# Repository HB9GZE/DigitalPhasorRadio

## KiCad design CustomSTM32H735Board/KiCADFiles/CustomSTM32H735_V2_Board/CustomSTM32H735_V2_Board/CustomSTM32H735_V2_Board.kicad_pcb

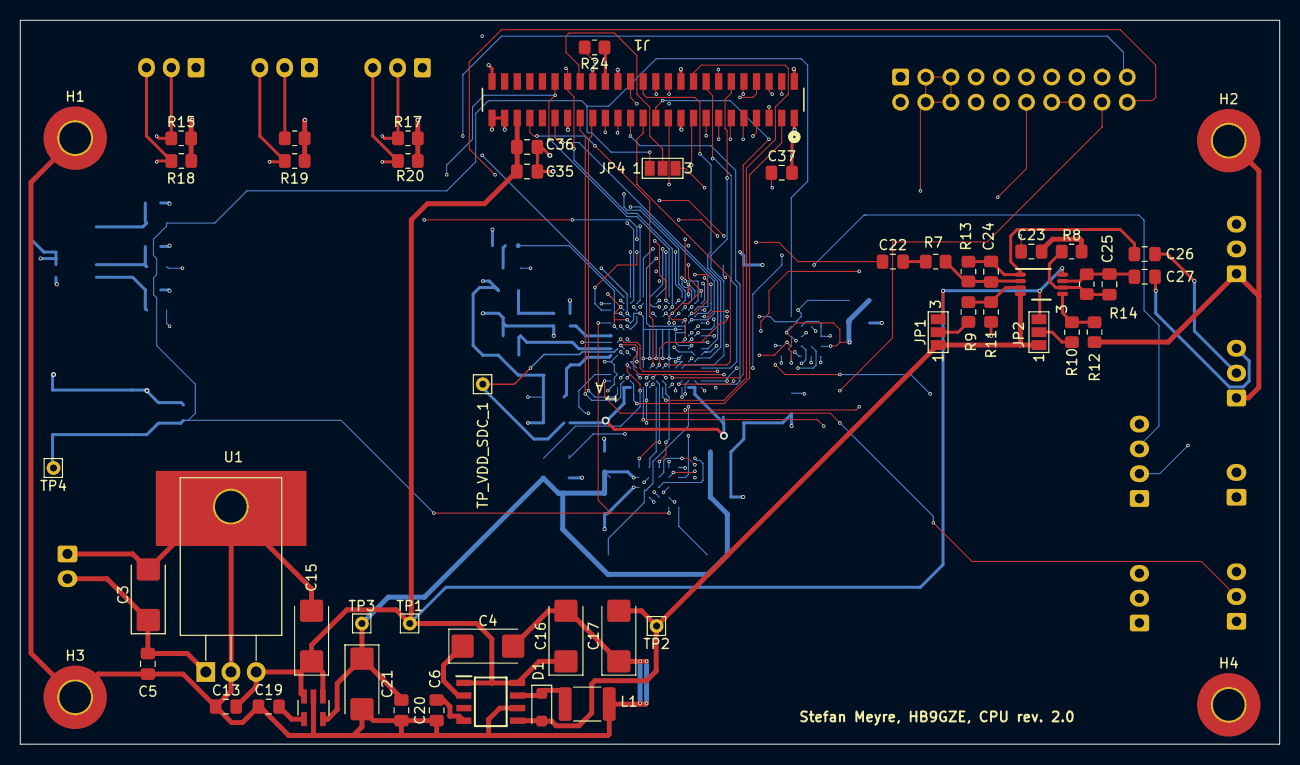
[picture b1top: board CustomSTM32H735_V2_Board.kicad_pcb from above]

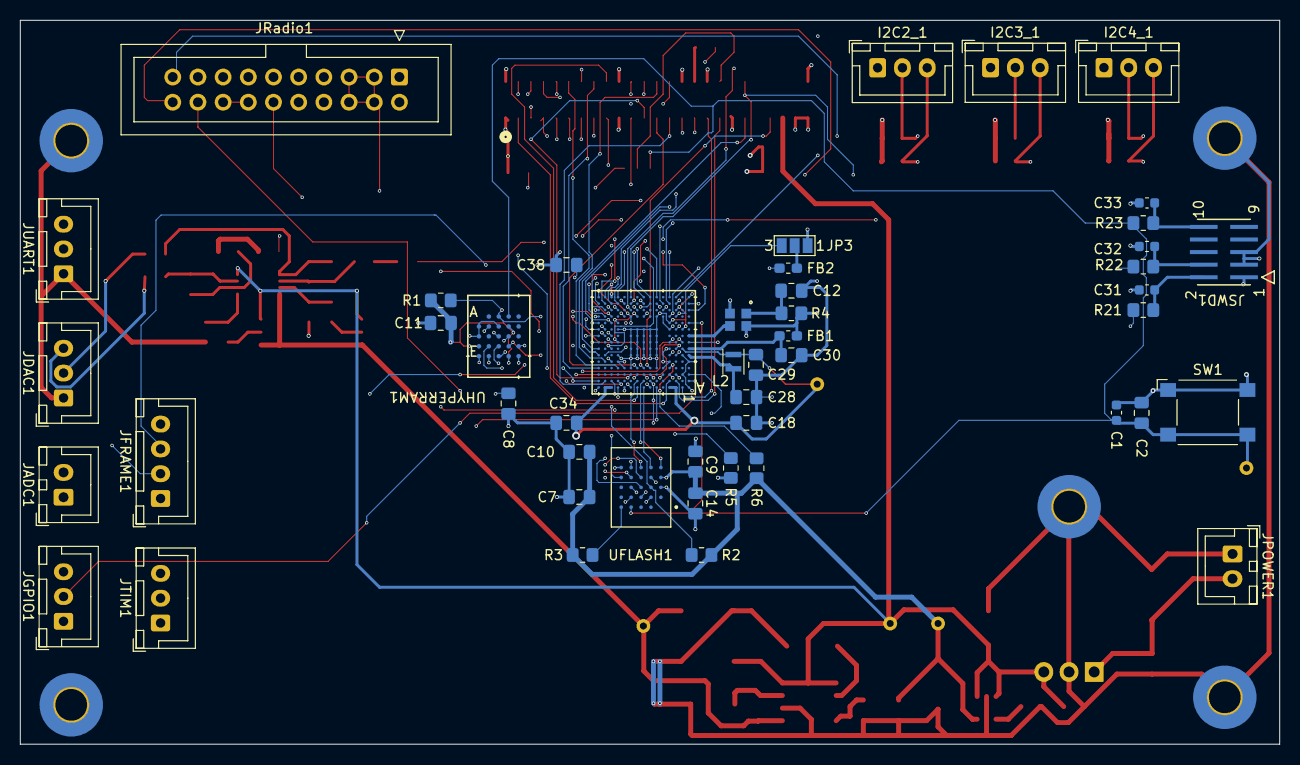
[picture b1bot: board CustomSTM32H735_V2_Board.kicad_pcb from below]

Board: 4 copper layers, 127.0 x 73.0 mm, 103 parts (48 on the bottom side), 122 nets.

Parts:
C1, C31, C32, C33: PGB1010603; C_0603_1608Metric
C2, C5, C7, C8, C9, C10, C11, C12, C13, C14, C20, C36, C37: 100nF; C_0805_2012Metric_Pad1.18x1.45mm_HandSolder
C3, C15: 47uF Tant. 25V; CP_EIA-6032-20_AVX-F_Pad2.25x2.35mm_HandSolder
C4, C21: 10uF Tant. 25V; CP_EIA-6032-20_AVX-F_Pad2.25x2.35mm_HandSolder
C6: optional: 82pF; C_0805_2012Metric_Pad1.18x1.45mm_HandSolder
C16: 1uF, Tant. 25V; CP_EIA-6032-20_AVX-F_Pad2.25x2.35mm_HandSolder
C17: 100uF Tant. 25V; CP_EIA-6032-20_AVX-F_Pad2.25x2.35mm_HandSolder
C18, C34, C38: 4.7uF low ESR; C_0805_2012Metric_Pad1.18x1.45mm_HandSolder
C19: 1uF; C_0805_2012Metric_Pad1.18x1.45mm_HandSolder
C22, C23, C26, C27, C29, C30, C35: 10uF; C_0805_2012Metric_Pad1.18x1.45mm_HandSolder
C24, C25: 1nF; C_0805_2012Metric_Pad1.18x1.45mm_HandSolder
C28: 220pF; C_0805_2012Metric_Pad1.18x1.45mm_HandSolder
D1: PMEG2010AEH; D_SOD-123F
FB1: FBMJ1608; L_0603_1608Metric_Pad1.05x0.95mm_HandSolder
FB2: FCM1608; L_0603_1608Metric_Pad1.05x0.95mm_HandSolder
H1, H2, H3, H4, H5: MountingHole_Pad; MountingHole_3.2mm_M3_Pad_TopBottom
I2C2_1, I2C3_1, I2C4_1: Conn_01x03_Socket; JST_XH_B3B-XH-A_1x03_P2.50mm_Vertical
IC1: NCP700BSN33T1G; SOT95P275X120-5N
J1: FLE-125-01-G-DV; CON50_2X25_UF_FLE_SAI
JADC1: Conn_01x02_Socket; JST_XH_B2B-XH-A_1x02_P2.50mm_Vertical
JDAC1: Conn_01x03_Socket; JST_XH_B3B-XH-A_1x03_P2.50mm_Vertical
JFRAME1: Conn_01x04_Socket; JST_XH_B4B-XH-A_1x04_P2.50mm_Vertical
JGPIO1: Conn_01x03_Socket; JST_XH_B3B-XH-A_1x03_P2.50mm_Vertical
JP1, JP2, JP3, JP4: SolderJumper_3_Open; SolderJumper-3_P1.3mm_Open_Pad1.0x1.5mm_NumberLabels
JPOWER1: Conn_01x02_Socket; JST_XH_B2B-XH-A_1x02_P2.50mm_Vertical
JRadio1: Conn_02x10_Odd_Even; IDC-Header_2x10_P2.54mm_Vertical
JSWD1: FTSH-105-01-L-DV-K; CON10_2X5_DUK_FTSH_SAI-M
JTIM1: Conn_01x03_Socket; JST_XH_B3B-XH-A_1x03_P2.50mm_Vertical
JUART1: Conn_01x03_Socket; JST_XH_B3B-XH-A_1x03_P2.50mm_Vertical
L1: 10uH; L_1812_4532Metric_Pad1.30x3.40mm_HandSolder
L2: 2.2uH; L_Murata_DFE201610P
PS1: TPS6735ID; SOIC127P600X175-8N
R1, R2, R3, R4, R6, R7, R8, R9, R10, R11, R12, R13, R14: 10k; R_0805_2012Metric_Pad1.20x1.40mm_HandSolder
R5: 5k1; R_0805_2012Metric_Pad1.20x1.40mm_HandSolder
R15, R16, R17, R18, R19, R20: 4.7k; R_0805_2012Metric_Pad1.20x1.40mm_HandSolder
R21, R22, R23: 22R; R_0805_2012Metric_Pad1.20x1.40mm_HandSolder
R24: 0R; R_0805_2012Metric_Pad1.20x1.40mm_HandSolder
SW1: SW_Omron_B3FS; SW_SPST_Omron_B3FS-100xP
TP1, TP2, TP3, TP4: TestPoint; Pin_D0.7mm_L6.5mm_W1.8mm_FlatFork
TP_VDD_SDC_1: TestPoint; Pin_D0.7mm_L6.5mm_W1.8mm_FlatFork
U1: L7805; TO-220-3_Horizontal_TabDown_GND_Pad
U2: OPA1678IDGKT; OPA1678_L
U3: STM32H735IGK6; BGA_735IGK6_STM
UFLASH1: MX25LM51245GXDI00; BGA24C100P5X5_600X800X120
UHYPERRAM1: IS66WVH16M8DBLL-100B1LI; TFBGA24_6X8_ISI
X1: NSC5004A-25M; NSC5004_NDK

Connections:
+3.3V: C7.1, C8.1, C9.1, C10.1, C11.1, C14.1, C20.1, C21.1, C37.1, FB1.1, IC1.5 (OUT), J1.50, JP3.1 (A), JSWD1.1, R1.1, R2.1, R3.1, R4.1, R6.2, R15.2, R16.2, R17.2, R18.2, R19.2, R20.2, TP3.1, U3.D5 (VDD), U3.D11 (VDD), U3.E4 (VDD), U3.E12 (VDD), U3.G4 (VDD), U3.H12 (VDD), U3.K4 (VDD), U3.L12 (VDD), U3.M5 (VDD), U3.M9 (VDD), UFLASH1.B4 (VCC), UFLASH1.D1 (VCCQ), UFLASH1.E4 (VCCQ__1), UHYPERRAM1.B4 (VCC), UHYPERRAM1.D1 (VCCQ), UHYPERRAM1.E4 (VCCQ), X1.4 (VCC)
+5V: C13.1, C15.1, C16.1, C35.1, C36.1, IC1.1 (IN), IC1.3 (EN), J1.45, JP1.3 (B), JP2.3 (B), PS1.1 (EN), PS1.8 (VCC), TP1.1, U1.3 (OUT), U2.8 (V+)
-5V: C17.2, D1.2 (A), JP1.1 (A), JP2.1 (A), PS1.5 (FB), TP2.1, U2.4 (V-)
/BOOT0: R5.1, U3.C5 (BOOT0)
/NRST: C1.2, C2.1, JP4.1 (A), R23.1, SW1.2, TP4.1, U3.L1 (NRST), UFLASH1.A4 (~RESET), UHYPERRAM1.A4 (RESET#)
/PA0: JFRAME1.4, U3.P1 (PA0-VSYNC_FREQ)
/PA0_C: JRadio1.19, U3.R3 (PA0_C-ADC1_INP0)
/PA1_C: JRadio1.20, U3.P3 (PA1_C-ADC2_INP1)
/PA3: J1.31, U3.N5 (PA3-LTDC_B5)
/PA4: J1.28, U3.P5 (PA4-LTDC_VSYNC)
/PA5: C23.1, U3.P6 (PA5-DAC1_OUT2)
/PA6: J1.8, U3.R7 (PA6-LTDC_G2)
/PA8: J1.27, U3.B14 (PA8-LTDC_B3)
/PA12: JRadio1.11, JRadio1.12, U3.B15 (PA12-LSBUSB)
/PA13: R21.1, U3.B13 (PA13(JTMS/SWDIO)-DEBUG_JTMS-SWDIO)
/PA14: R22.1, U3.A12 (PA14(JTCK/SWCLK)-DEBUG_JTCK-SWCLK)
/PA15: JTIM1.2, U3.A11 (PA15(JTDI)-TIM2_CH1)
/PB0: J1.6, U3.R8 (PB0-LTDC_G1)
/PB1: J1.4, U3.M8 (PB1-LTDC_G0)
/PB2: U3.P7 (PB2-OCTOSPIM_P1_DQS), UFLASH1.C3 (DQS)
/PB3: JTIM1.3, U3.A6 (PB3(JTDO/TRACESWO)-TIM2_CH2)
/PB8: J1.33, U3.A2 (PB8-LTDC_B6)
/PB9: J1.35, U3.B3 (PB9-LTDC_B7)
/PB10: I2C2_1.3, R20.1, U3.N12 (PB10-I2C2_SCL)
/PB11: I2C2_1.2, R17.1, U3.P10 (PB11-I2C2_SDA)
/PB12: JRadio1.13, JRadio1.15, U3.M15 (PB12-S0)
/PB13: JRadio1.14, JRadio1.16, U3.L15 (PB13-S1)
/PB14: JFRAME1.3, U3.K15 (PB14-FRAME_RATE)
/PB15: JFRAME1.2, U3.K14 (PB15-MCU_ACTIVE)
/PC2_C: JADC1.2, U3.N1 (PC2_C-ADC3_INP0)
/PC4: C22.1, U3.R6 (PC4-OPAMP1_VOUT)
/PC6: J1.26, U3.E14 (PC6-LTDC_HSYNC)
/PC7: J1.16, U3.D15 (PC7-LTDC_G6)
/PC9: I2C3_1.2, R16.1, U3.E13 (PC9-I2C3_SDA)
/PC13: JGPIO1.3, U3.C1 (PC13-GPIO_PC13)
/PD0: J1.23, U3.C10 (PD0-LTDC_B1)
/PD1: JUART1.3, U3.A10 (PD1-UART4_TX)
/PD3: J1.18, U3.A9 (PD3-LTDC_G7)
/PD4: U3.C9 (PD4-OCTOSPIM_P1_IO4), UFLASH1.D5 (SIO4)
/PD5: U3.B9 (PD5-OCTOSPIM_P1_IO5), UFLASH1.E3 (SIO5)
/PD6: J1.25, U3.D9 (PD6-LTDC_B2)
/PD7: U3.B8 (PD7-OCTOSPIM_P1_IO7), UFLASH1.E1 (SIO7)
/PD10: J1.24, U3.L13 (PD10-LCD_DISP)
/PD11: U3.J13 (PD11-OCTOSPIM_P1_IO0), UFLASH1.D3 (SI/SIO0)
/PD12: U3.J15 (PD12-OCTOSPIM_P1_IO1), UFLASH1.D2 (SO/SIO1)
/PD13: U3.H15 (PD13-OCTOSPIM_P1_IO3), UFLASH1.D4 (SIO3)
/PDR_ON: R6.1, U3.D4 (PDR_ON)
/PE0: J1.3, U3.B4 (PE0-LTDC_R0)
/PE1: J1.15, U3.C4 (PE1-LTDC_R6)
/PE2: U3.C3 (PE2-OCTOSPIM_P1_IO2), UFLASH1.C4 (SIO2)
/PE4: JGPIO1.2, U3.B1 (PE4-GPIO_PE4)
/PE11: J1.10, U3.R12 (PE11-LTDC_G3)
/PE12: J1.29, U3.P12 (PE12-LTDC_B4)
/PE13: J1.22, U3.P13 (PE13-LTDC_DE)
/PE15: J1.17, U3.P14 (PE15-LTDC_R7)
/PF0: U3.F4 (PF0-OCTOSPIM_P2_IO0), UHYPERRAM1.D3 (DQ0)
/PF1: U3.F3 (PF1-OCTOSPIM_P2_IO1), UHYPERRAM1.D2 (DQ1)
/PF2: U3.G3 (PF2-OCTOSPIM_P2_IO2), UHYPERRAM1.C4 (DQ2)
/PF3: U3.H4 (PF3-OCTOSPIM_P2_IO3), UHYPERRAM1.D4 (DQ3)
/PF4: U3.H2 (PF4-OCTOSPIM_P2_CLK), UHYPERRAM1.B2 (CK)
/PF6: JRadio1.17, U3.H1 (PF6-TIM23_CH1)
/PF10: U3.K3 (PF10-OCTOSPIM_P1_CLK), UFLASH1.B2 (SCLK)
/PF12: U3.P11 (PF12-OCTOSPIM_P2_DQS), UHYPERRAM1.C3 (RWDS)
/PF14: I2C4_1.3, J1.40, R18.1, U3.R10 (PF14-I2C4_SCL)
/PF15: I2C4_1.2, J1.38, R15.1, U3.N10 (PF15-I2C4_SDA)
/PG0: U3.P8 (PG0-OCTOSPIM_P2_IO4), UHYPERRAM1.D5 (DQ4)
/PG1: U3.N9 (PG1-OCTOSPIM_P2_IO5), UHYPERRAM1.E3 (DQ5)
/PG2: J1.39, U3.G15 (PG2-CTP_INT)
/PG3: JFRAME1.1, U3.H13 (PG3-RENDER_TIME)
/PG5: JRadio1.3, JRadio1.4, JRadio1.5, JRadio1.6, U3.F15 (PG5-RXTX)
/PG6: R2.2, U3.F14 (PG6-OCTOSPIM_P1_NCS), UFLASH1.C2 (~CS)
/PG7: R24.2, U3.G13 (PG7-LTDC_CLK)
/PG9: U3.A8 (PG9-OCTOSPIM_P1_IO6), UFLASH1.E2 (SIO6)
/PG10: U3.C8 (PG10-OCTOSPIM_P2_IO6), UHYPERRAM1.E2 (DQ6)
/PG11: U3.A7 (PG11-OCTOSPIM_P2_IO7), UHYPERRAM1.E1 (DQ7)
/PG12: R1.2, U3.D8 (PG12-OCTOSPIM_P2_NCS), UHYPERRAM1.A3 (CS#)
/PG13: JRadio1.18, U3.B7 (PG13-TIM23_CH2)
/PG14: J1.21, U3.C7 (PG14-LTDC_B0)
/PG15: J1.43, U3.D7 (PG15-LCD_BL_CTRL)
/PH0: U3.J1 (PH0-OSC_IN-RCC_OSC_IN), X1.3 (OUTPUT)
/PH3: J1.5, U3.R4 (PH3-LTDC_R1)
/PH4: J1.14, U3.P4 (PH4-LTDC_G5)
/PH6: JP4.3 (B), U3.P15 (PH6-LCD_RST)
/PH7: I2C3_1.3, R19.1, U3.M11 (PH7-I2C3_SCL)
/PH8: J1.7, U3.N13 (PH8-LTDC_R2)
/PH9: J1.9, U3.M14 (PH9-LTDC_R3)
/PH10: J1.11, U3.N14 (PH10-LTDC_R4)
/PH11: J1.13, U3.M13 (PH11-LTDC_R5)
/PH12: JRadio1.7, JRadio1.8, JRadio1.9, JRadio1.10, U3.N15 (PH12-NRXTX)
/PH14: JUART1.2, U3.B12 (PH14-UART4_RX)
/PH15: J1.12, U3.D12 (PH15-LTDC_G4)
/VDDSMPS: C30.1, FB1.2, U3.G1 (VDDSMPS)
/VDD_SDC: C18.2, C29.1, C34.2, C38.2, L2.1, TP_VDD_SDC_1.1, U3.A3 (VDDLDO), U3.A4 (VCAP), U3.A13 (VDDLDO), U3.A14 (VCAP), U3.G2 (VFBSMPS), U3.R13 (VCAP), U3.R14 (VDDLDO)
/VLXSMPS: C28.2, L2.2, U3.F1 (VLXSMPS)
GND: C1.1, C2.2, C3.2, C4.2, C5.2, C6.2, C7.2, C8.2, C9.2, C10.2, C11.2, C12.1, C13.2, C14.2, C15.2, C16.2, C17.1, C18.1, C19.1, C20.2, C21.2, C28.1, C29.2, C30.2, C31.2, C32.1, C33.1, C34.1, C35.2, C36.2, C37.2, C38.1, H1.1, H2.1, H3.1, H4.1, H5.1, I2C2_1.1, I2C3_1.1, I2C4_1.1, IC1.2 (GND), J1.1, J1.2, J1.19, J1.20, J1.30, J1.34, J1.37, J1.47, J1.49, JADC1.1, JDAC1.1, JGPIO1.1, JPOWER1.1, JRadio1.1, JRadio1.2, JSWD1.3, JSWD1.5, JTIM1.1, JUART1.1, L1.2, PS1.6 (GND), R5.2, R11.1, R12.1, SW1.1, U1.2 (GND), U1.4, U3.A1 (VSS), U3.A15 (VSS), U3.C2 (VSS), U3.D6 (VSS), U3.D10 (VSS), U3.E1 (VSS), U3.F2 (VSSSMPS), U3.F6 (VSS), U3.F7 (VSS), U3.F8 (VSS), U3.F9 (VSS), U3.F10 (VSS), U3.F12 (VSS), U3.G6 (VSS), U3.G7 (VSS), U3.G8 (VSS), U3.G9 (VSS), U3.G10 (VSS), U3.H6 (VSS), U3.H7 (VSS), U3.H8 (VSS), U3.H9 (VSS), U3.H10 (VSS), U3.J6 (VSS), U3.J7 (VSS), U3.J8 (VSS), U3.J9 (VSS), U3.J10 (VSS), U3.J14 (VSS), U3.K2 (VSS), U3.K6 (VSS), U3.K7 (VSS), U3.K8 (VSS), U3.K9 (VSS), U3.K10 (VSS), U3.K12 (VSS), U3.L4 (VREF-), U3.M6 (VSS), U3.M10 (VSS), U3.N3 (VSSA), U3.R1 (VSS), U3.R15 (VSS), UFLASH1.B3 (GND), UFLASH1.C1 (VSSQ), UFLASH1.E5 (VSSQ__1), UHYPERRAM1.B1 (CK#), UHYPERRAM1.B3 (VSS), UHYPERRAM1.C1 (VSSQ), UHYPERRAM1.E5 (VSSQ), X1.2 (GND)
unnamed: C22.2, R7.2
unnamed: C23.2, R8.2
unnamed: C31.1, JSWD1.2, R21.2
unnamed: C32.2, JSWD1.4, R22.2
unnamed: C33.2, JSWD1.10, R23.2
unnamed: D1.1 (K), L1.1, PS1.7 (OUT)
unnamed: C19.2, IC1.4 (BYP)
unnamed: J1.32, R24.1
unnamed: C26.2, JDAC1.2
unnamed: C27.2, JDAC1.3
unnamed: JP1.2 (C), R9.2
unnamed: JP2.2 (C), R10.2
unnamed: JP3.3 (B), U3.M3 (VREF+)
unnamed: FB2.1, JP3.2 (C)
unnamed: J1.36, JP4.2 (C)
unnamed: C3.1, C5.1, JPOWER1.2, U1.1 (IN)
unnamed: C6.1, PS1.4 (COMP)
unnamed: C4.1, PS1.2 (REF)
unnamed: R9.1, R11.2, U2.3 (IN+)
unnamed: C24.1, R7.1, R13.2, U2.2 (IN-)
unnamed: C24.2, C26.1, R13.1, U2.1 (OUT)
unnamed: R10.1, R12.2, U2.5 (IN+)
unnamed: C25.1, R8.1, R14.2, U2.6 (IN-)
unnamed: C25.2, C27.1, R14.1, U2.7 (OUT)
unnamed: FB2.2, U3.M4 (VDDA)
unnamed: R3.2, UFLASH1.A5 (~ECS)
unnamed: C12.2, R4.2, X1.1 (STAND-BY)

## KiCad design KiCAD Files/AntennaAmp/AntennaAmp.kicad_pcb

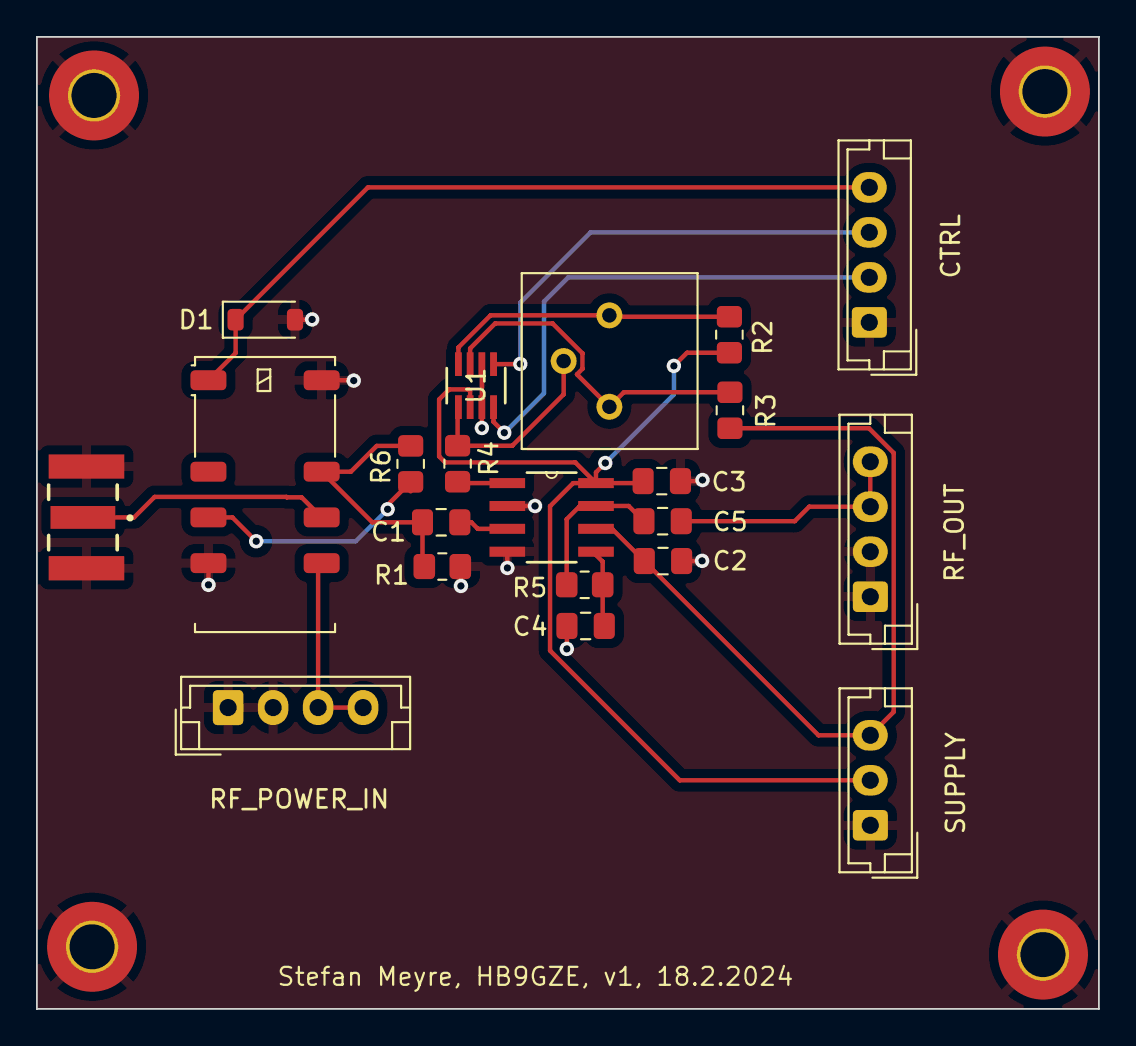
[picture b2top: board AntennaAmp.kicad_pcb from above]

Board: 2 copper layers, 59.0 x 54.0 mm, 25 parts (0 on the bottom side), 18 nets.

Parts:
C1, C2, C3, C5: 100nF; C_0805_2012Metric_Pad1.18x1.45mm_HandSolder
C4: 5.6pF; C_0805_2012Metric_Pad1.18x1.45mm_HandSolder
CTRL: CTRL; JST_EH_B4B-EH-A_1x04_P2.50mm_Vertical
D1: 1N4148W; D_SOD-123
H1, H2, H3, H4: MountingHole_Pad; MountingHole_2.5mm_Pad_TopBottom
J1: SMA; SAMTEC_SMA-J-P-H-ST-EM1
K1: EE2-3NUH; Relay_DPDT_Kemet_EE2_NUH
R1, R4: 100R; R_0805_2012Metric_Pad1.20x1.40mm_HandSolder
R2, R3: 10k; R_0805_2012Metric_Pad1.20x1.40mm_HandSolder
R5, R6: 0R; R_0805_2012Metric_Pad1.20x1.40mm_HandSolder
RF_OUT: RF_OUT; JST_EH_B4B-EH-A_1x04_P2.50mm_Vertical
RF_POWER_IN: RF_POWER_IN; JST_EH_B4B-EH-A_1x04_P2.50mm_Vertical
RV1: 5k; Potentiometer_Bourns_3386P_Vertical
SUPPLY: SUPPLY; JST_EH_B3B-EH-A_1x03_P2.50mm_Vertical
U1: AD5245BRJZ5-RL7; AD5245
U2: AD603ARZ; AD603

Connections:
+5V: C3.2, R2.1, SUPPLY.2, U1.2 (VDD), U2.8 (VPOS)
-5V: C2.1, R3.1, SUPPLY.3, U2.6 (VNEG)
/A: R2.2, RV1.1, U1.8 (A)
/B: R3.2, RV1.3, U1.7 (B)
/PTT: CTRL.4, D1.1 (K), K1.1
/RF1: J1.1, K1.9
/RF2: C1.1, K1.10, R1.1, R6.1
/RF3: C1.2, U2.3 (VINP)
/RF_PWR_IN: K1.8, RF_POWER_IN.3, RF_POWER_IN.4
/SCL: CTRL.2, U1.4 (SCL)
/SDA: CTRL.3, U1.5 (SDA)
/W: R4.1, RV1.2, U1.1 (W)
GND: C2.2, C3.1, C4.1, CTRL.1, D1.2 (A), H1.1, H2.1, H3.1, H4.1, J1.2_1, J1.2_2, J1.3_1, J1.3_2, K1.5, K1.12, R1.2, RF_OUT.1, RF_OUT.2, RF_POWER_IN.1, RF_POWER_IN.2, SUPPLY.1, U1.3 (GND), U1.6 (AD0), U2.2 (GNEG), U2.4 (COMM)
unnamed: K1.4, R6.2
unnamed: C5.2, RF_OUT.3, RF_OUT.4
unnamed: C4.2, R5.1, U2.5 (FDBK)
unnamed: R4.2, U2.1 (GPOS)
unnamed: C5.1, R5.2, U2.7 (VOUT)

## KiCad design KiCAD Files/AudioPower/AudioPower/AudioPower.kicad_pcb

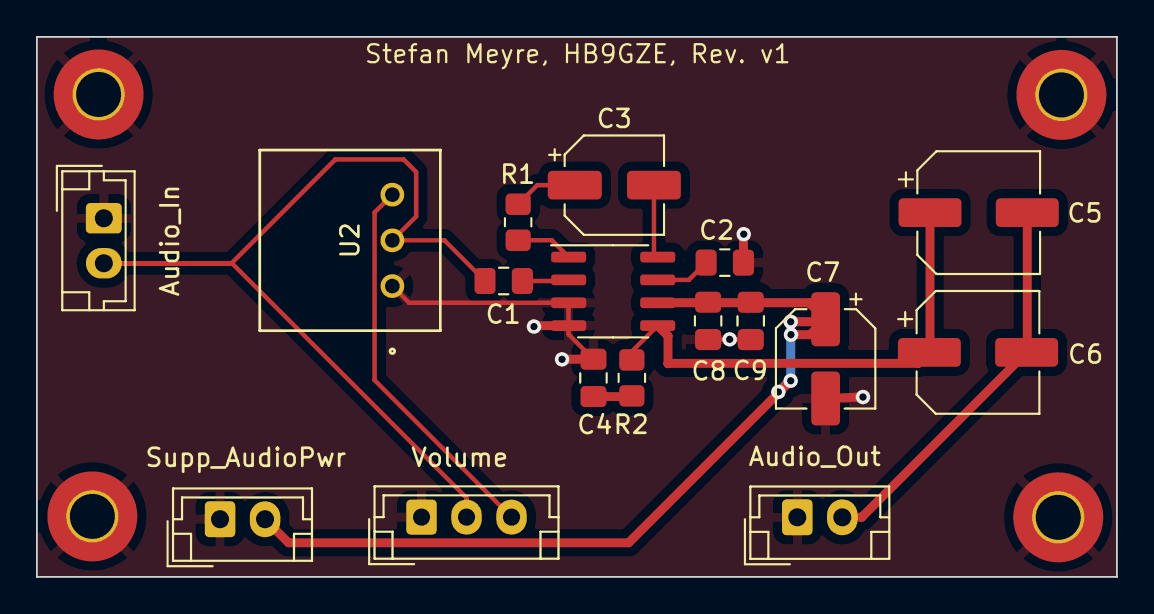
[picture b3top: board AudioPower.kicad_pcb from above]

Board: 2 copper layers, 60.0 x 30.0 mm, 21 parts (0 on the bottom side), 12 nets.

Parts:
Audio_In: Conn_01x02_Socket; JST_EH_B2B-EH-A_1x02_P2.50mm_Vertical
Audio_Out: Conn_01x02_Socket; JST_EH_B2B-EH-A_1x02_P2.50mm_Vertical
C1, C2, C8: 1uF; C_0805_2012Metric_Pad1.18x1.45mm_HandSolder
C3, C7: 10uF; CP_Elec_5x3.9
C4: 50nF; C_0805_2012Metric_Pad1.18x1.45mm_HandSolder
C5, C6: 100uF; CP_Elec_6.3x5.7
C9: 100nF; C_0805_2012Metric_Pad1.18x1.45mm_HandSolder
H1, H2, H3, H4: MountingHole_Pad; MountingHole_2.5mm_Pad_TopBottom
R1: 1.2k; R_0805_2012Metric_Pad1.20x1.40mm_HandSolder
R2: 10R; R_0805_2012Metric_Pad1.20x1.40mm_HandSolder
Supp_AudioPwr: Supp_AudioPwr; JST_EH_B2B-EH-A_1x02_P2.50mm_Vertical
U1: LM386; SOIC-8_3.9x4.9mm_P1.27mm
U2: 3310R-125-103L
Volume: Volume; JST_EH_B3B-EH-A_1x03_P2.50mm_Vertical

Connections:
+12V: C7.1, C8.1, C9.1, Supp_AudioPwr.2, U1.6 (V+)
/Audio_In: Audio_In.2, C1.1, U2.2, Volume.2
/Audio_Out: Audio_Out.2, C5.2, C6.2
GND: Audio_In.1, Audio_Out.1, C2.2, C4.1, C7.2, C8.2, C9.2, H1.1, H2.1, H3.1, H4.1, Supp_AudioPwr.1, U1.3 (+), U1.4 (GND), U2.1, Volume.1
unnamed: C3.1, R1.1
unnamed: C3.2, U1.8 (GAIN)
unnamed: C4.2, R2.1
unnamed: C5.1, C6.1, R2.2, U1.5
unnamed: R1.2, U1.1 (GAIN)
unnamed: C1.2, U1.2 (-)
unnamed: C2.1, U1.7 (BYPASS)
unnamed: U2.3, Volume.3

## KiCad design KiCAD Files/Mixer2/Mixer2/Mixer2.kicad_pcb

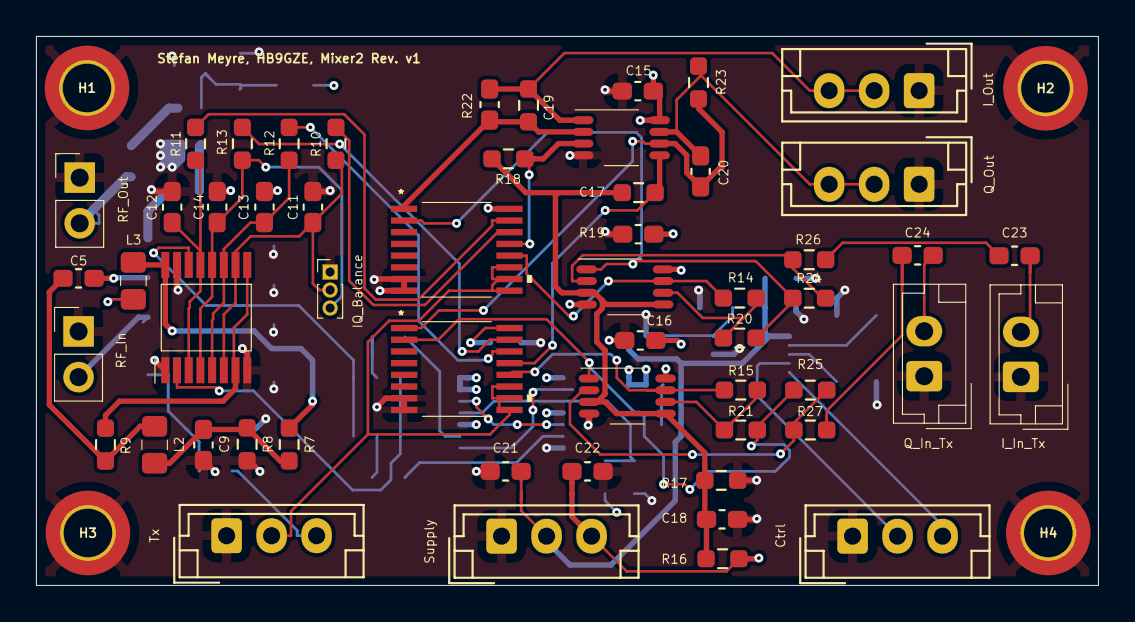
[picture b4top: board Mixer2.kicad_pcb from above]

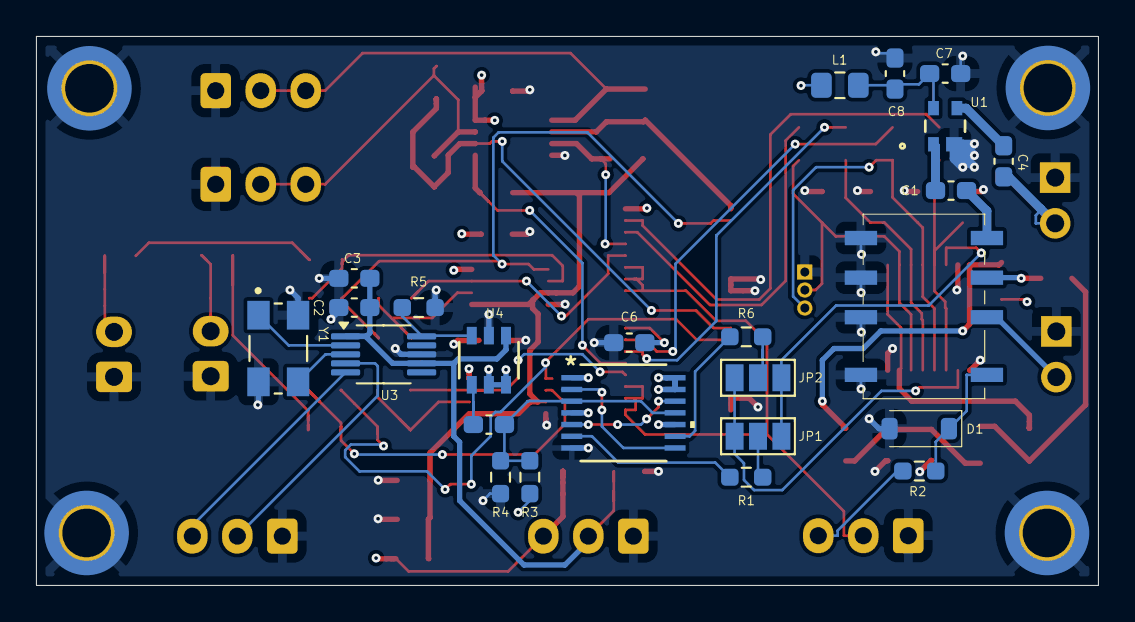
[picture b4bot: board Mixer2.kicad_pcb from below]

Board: 4 copper layers, 59.0 x 30.5 mm, 83 parts (24 on the bottom side), 59 nets.

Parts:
C1, C2, C3, C4, C5, C8, C9, C10, C15, C16, C17, C18, C21, C22: 100nF; C_0603_1608Metric_Pad1.08x0.95mm_HandSolder
C6: 10uF; C_0603_1608Metric_Pad1.08x0.95mm_HandSolder
C7, C23, C24: 1uF; C_0603_1608Metric_Pad1.08x0.95mm_HandSolder
C11, C12, C13, C14: 47nF; C_0603_1608Metric_Pad1.08x0.95mm_HandSolder
C19, C20: 1.5nF; C_0603_1608Metric_Pad1.08x0.95mm_HandSolder
Ctrl: Conn_01x03_Socket; JST_EH_B3B-EH-A_1x03_P2.50mm_Vertical
D1: 1N4148W; D_SOD-123
H1, H2, H3, H4: MountingHole_Pad; MountingHole_2.7mm_M2.5_DIN965_Pad_TopBottom
IC1: FST3253MTCX; SOP65P640X110-16N
IQ_Balance: Conn_01x03; PinHeader_1x03_P1.00mm_Vertical
I_In_Tx: Conn_01x02; JST_EH_B2B-EH-A_1x02_P2.50mm_Vertical
I_Out: I_Out; JST_EH_B3B-EH-A_1x03_P2.50mm_Vertical
JP1, JP2: SolderJumper_3_Open; SolderJumper-3_P1.3mm_Open_Pad1.0x1.5mm_NumberLabels
K1: G6K-2F-Y DC3; G6K-2F-Y DC3_OMR
L1, L2, L3: 100u; L_0805_2012Metric_Pad1.15x1.40mm_HandSolder
Q_In_Tx: Conn_01x02; JST_EH_B2B-EH-A_1x02_P2.50mm_Vertical
Q_Out: Q_Out; JST_EH_B3B-EH-A_1x03_P2.50mm_Vertical
R1, R6: 100R; R_0603_1608Metric_Pad0.98x0.95mm_HandSolder
R2: 0R; R_0603_1608Metric_Pad0.98x0.95mm_HandSolder
R3, R4, R7, R8, R16, R17: 10k; R_0603_1608Metric_Pad0.98x0.95mm_HandSolder
R5: DNF; R_0603_1608Metric_Pad0.98x0.95mm_HandSolder
R9, R10, R11, R12, R13: 47R; R_0603_1608Metric_Pad0.98x0.95mm_HandSolder
R14, R15, R18, R19, R20, R21, R22, R23, R24, R25, R26, R27: 10k 1%; R_0603_1608Metric_Pad0.98x0.95mm_HandSolder
RF_In: Conn_01x02; PinHeader_1x02_P2.54mm_Vertical
RF_Out: Conn_01x02; PinHeader_1x02_P2.54mm_Vertical
Supply: Supply; JST_EH_B3B-EH-A_1x03_P2.50mm_Vertical
Tx: Q_Out; JST_EH_B3B-EH-A_1x03_P2.50mm_Vertical
U1: BGA420H6327XTSA1; PG-SOT343-4-1_INF
U2: SN74AC74PWR; 74AC74-L
U3: Si5351A-B-GT; MSOP-10_3x3mm_P0.5mm
U4: TXU0101DBVR; SOT-23-6-DBV_TEX
U5, U6: 4053; TSSOP16_5P1X4P5_NEX
U7, U8, U9: OPA1678IDGKT; OPA1678_L
Y1: ECS-250-8-30B-CKM; XTAL_ECS-250-8-30B-CKM

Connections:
+3.3V: C2.2, C3.2, C21.2, Supply.2, U3.1 (VDD), U3.7 (VDDO), U4.1 (VCCA)
+5V: C6.2, C15.2, C16.2, C17.2, C22.2, L1.1, L3.1, R4.1, R16.2, Supply.3, U2.1 (*1CLR), U2.4 (*1PRE), U2.10 (*2PRE), U2.13 (*2CLR), U2.14 (VCC), U4.5 (OE), U4.6 (VCCB), U5.16 (VDD), U6.16 (VDD), U7.8 (V+), U8.8 (V+), U9.8 (V+)
/1: C11.2, IC1.6 (1B1), IC1.10 (2B1), IQ_Balance.2, R10.1
/2: C13.2, IC1.5 (1B2), IC1.11 (2B2), R12.1
/3: C14.2, IC1.4 (1B3), IC1.12 (2B3), IQ_Balance.3, R13.1
/4: C12.2, IC1.3 (1B4), IC1.13 (2B4), R11.1
/+2.5V: C18.2, R16.1, R17.1, R18.2, R19.2, U8.3 (IN+), U8.5 (IN+), U9.3 (IN+), U9.5 (IN+)
/Clk_S0: JP2.2 (C), R6.1
/Clk_S1: JP1.2 (C), R1.2
/RF_IN_OUT: C5.1, K1.3
/RF_In: K1.2, RF_In.2
/RF_Out: C4.2, RF_Out.2
/RawClk: R5.1, U3.10 (CLK0), U4.3 (A)
/S0: IC1.14 (S0), JP1.1 (A), JP2.1 (A)
/S1: IC1.2 (S1), JP1.3 (B), JP2.3 (B)
/SCL: Ctrl.2, U3.4 (SCL)
/SDA: Ctrl.3, U3.5 (SDA)
/SI5351CLK: C10.2, R3.1, R4.2, U2.3 (1CLK), U2.11 (2CLK)
/Tx: Tx.2, U5.9 (C), U5.10 (B), U5.11 (A), U6.9 (C), U6.10 (B), U6.11 (A)
/TxN: R2.2, Tx.3
GND: C2.1, C3.1, C6.1, C7.1, C8.1, C9.1, C11.1, C12.1, C13.1, C14.1, C15.1, C16.1, C17.1, C18.1, C21.1, C22.1, Ctrl.1, D1.2 (A), H1.1, H2.1, H3.1, H4.1, IC1.1 (~OE1), IC1.8 (GND), IC1.15 (~OE2), IQ_Balance.1, I_In_Tx.1, I_Out.1, K1.5, K1.6, K1.7, K1.8, Q_In_Tx.1, Q_Out.1, R3.2, R5.2, R8.2, R17.2, RF_In.1, RF_Out.1, Supply.1, Tx.1, U1.2 (GND), U2.7 (GND), U3.8 (GND), U4.2 (GND), U5.7 (VEE), U5.8 (VSS), U6.7 (VEE), U6.8 (VSS), U7.4 (V-), U8.4 (V-), U9.4 (V-), Y1.2 (GND), Y1.4 (GND__1)
unnamed: C1.1, K1.4
unnamed: C5.2, L2.2, R9.1
unnamed: C9.2, L2.1, R7.2, R8.1
unnamed: C23.2, R26.2
unnamed: C24.2, R27.2
unnamed: D1.1 (K), K1.1, R2.1
unnamed: IC1.7 (1A), IC1.9 (2A), R9.2
unnamed: IC1.16 (VCC), L3.2, R7.1
unnamed: C23.1, I_In_Tx.2
unnamed: C19.1, I_Out.2, I_Out.3, R22.2, U7.1 (OUT)
unnamed: C24.1, Q_In_Tx.2
unnamed: C20.1, Q_Out.2, Q_Out.3, R23.2, U7.7 (OUT)
unnamed: C1.2, U1.1 (IN)
unnamed: C4.1, U1.3 (OUT)
unnamed: C7.2, C8.2, L1.2, U1.4 (VD)
unnamed: U2.5 (1Q), U2.12 (2D)
unnamed: R6.2, U2.9 (2Q)
unnamed: R1.1, U2.6 (*1Q)
unnamed: U2.2 (1D), U2.8 (*2Q)
unnamed: U3.2 (XA), Y1.1 (IN/OUT)
unnamed: U3.3 (XB), Y1.3 (OUT/IN)
unnamed: C10.1, U4.4 (BY)
unnamed: R14.1, U5.12 (X0), U8.7 (OUT)
unnamed: R18.1, U5.13 (X1), U7.3 (IN+)
unnamed: R10.2, U5.14 (X)
unnamed: R20.2, R24.1, U5.2 (Y0), U8.1 (OUT)
unnamed: C19.2, R22.1, U5.1 (Y1), U7.2 (IN-)
unnamed: R11.2, U5.15 (Y)
unnamed: R15.1, U6.12 (X0), U9.7 (OUT)
unnamed: R19.1, U6.13 (X1), U7.5 (IN+)
unnamed: R12.2, U6.14 (X)
unnamed: R21.2, R25.1, U6.2 (Y0), U9.1 (OUT)
unnamed: C20.2, R23.1, U6.1 (Y1), U7.6 (IN-)
unnamed: R13.2, U6.15 (Y)
unnamed: R24.2, R26.1, U8.2 (IN-)
unnamed: R14.2, R20.1, U8.6 (IN-)
unnamed: R25.2, R27.1, U9.2 (IN-)
unnamed: R15.2, R21.1, U9.6 (IN-)

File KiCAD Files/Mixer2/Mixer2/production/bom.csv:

Designator,Footprint,Quantity,Value,LCSC Part #
"C1, C10, C15, C16, C17, C18, C2, C21, C22, C3, C4, C5, C8, C9",0603,14,100nF,
"C11, C12, C13, C14",0603,4,47nF,
"C19, C20",0603,2,1.5nF,
"C23, C24, C7",0603,3,1uF,
C6,0603,1,10uF,
Ctrl,JST_EH_B3B-EH-A_1x03_P2.50mm_Vertical,1,Conn_01x03_Socket,
D1,D_SOD-123,1,1N4148W,
"H1, H2, H3, H4",MountingHole_2.7mm_M2.5_DIN965_Pad_TopBottom,4,MountingHole_Pad,
IC1,SOP65P640X110-16N,1,FST3253MTCX,
IQ_Balance,PinHeader_1x03_P1.00mm_Vertical,1,Conn_01x03,
"I_In_Tx, Q_In_Tx",JST_EH_B2B-EH-A_1x02_P2.50mm_Vertical,2,Conn_01x02,
I_Out,JST_EH_B3B-EH-A_1x03_P2.50mm_Vertical,1,I_Out,
K1,G6K-2F-Y DC3_OMR,1,G6K-2F-Y DC3,
"L1, L2, L3",0805,3,100u,
"Q_Out, Tx",JST_EH_B3B-EH-A_1x03_P2.50mm_Vertical,2,Q_Out,
"R1, R6",0603,2,100R,
"R10, R11, R12, R13, R9",0603,5,47R,
"R14, R15, R18, R19, R20, R21, R22, R23, R24, R25, R26, R27",0603,12,10k 1%,
"R16, R17, R3, R4, R7, R8",0603,6,10k,
R2,0603,1,0R,
R5,0603,1,DNF,
"RF_In, RF_Out",PinHeader_1x02_P2.54mm_Vertical,2,Conn_01x02,
Supply,JST_EH_B3B-EH-A_1x03_P2.50mm_Vertical,1,Supply,
U1,PG-SOT343-4-1_INF,1,BGA420H6327XTSA1,
U2,74AC74-L,1,SN74AC74PWR,
U3,MSOP-10_3x3mm_P0.5mm,1,Si5351A-B-GT,
U4,SOT-23-6-DBV_TEX,1,TXU0101DBVR,
"U5, U6",TSSOP16_5P1X4P5_NEX,2,4053,
"U7, U8, U9",OPA1678_L,3,OPA1678IDGKT,
Y1,XTAL_ECS-250-8-30B-CKM,1,ECS-250-8-30B-CKM,

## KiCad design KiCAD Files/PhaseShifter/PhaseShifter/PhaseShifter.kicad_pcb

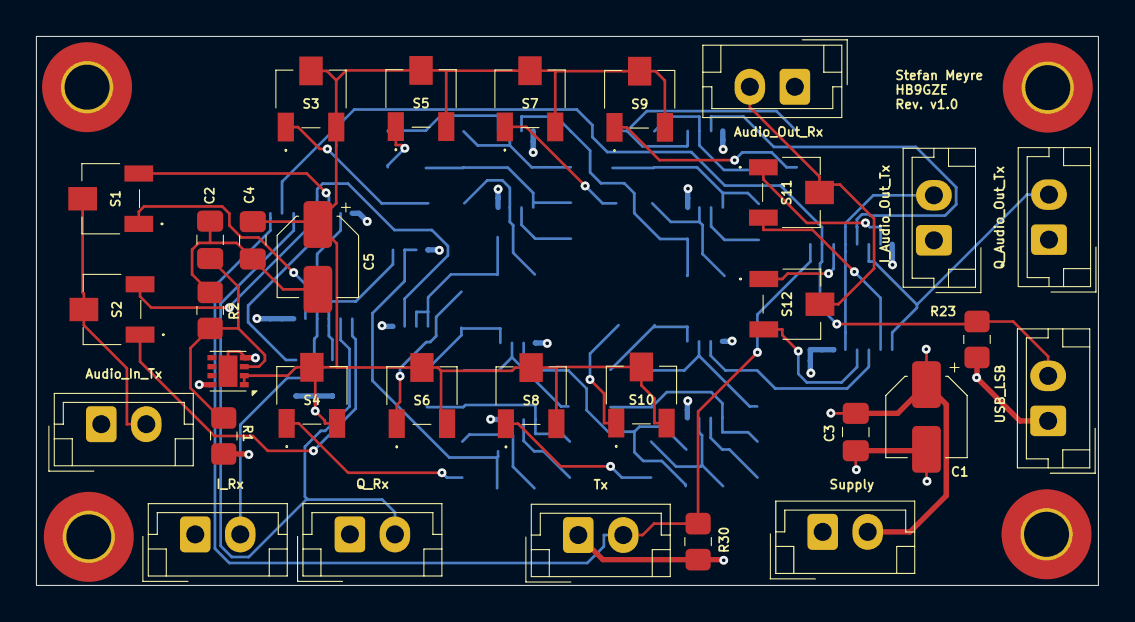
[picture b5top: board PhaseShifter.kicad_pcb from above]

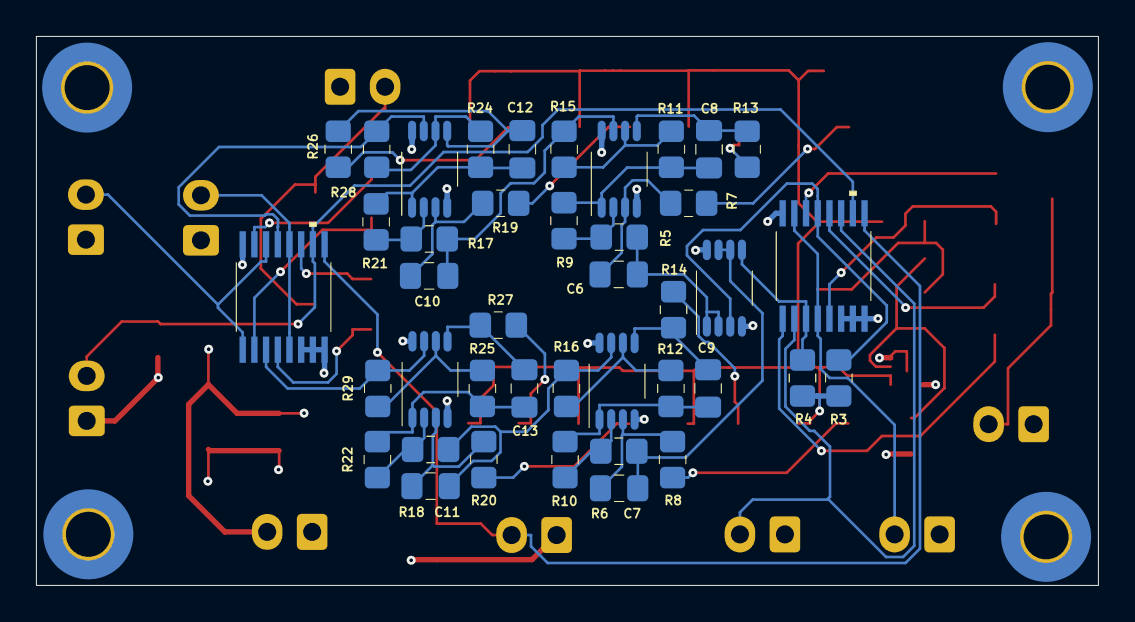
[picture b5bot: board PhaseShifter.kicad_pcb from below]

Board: 4 copper layers, 59.0 x 30.5 mm, 76 parts (41 on the bottom side), 57 nets.

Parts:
Audio_In_Tx: Conn_01x02_Socket; JST_EH_B2B-EH-A_1x02_P2.50mm_Vertical
Audio_Out_Rx: Conn_01x02_Socket; JST_EH_B2B-EH-A_1x02_P2.50mm_Vertical
C1: 100uF; CP_Elec_4x3.9
C2, C4, C6, C7, C8, C9, C10, C11, C12, C13: 10nF; C_0805_2012Metric_Pad1.18x1.45mm_HandSolder
C3: 100nF; C_0805_2012Metric_Pad1.18x1.45mm_HandSolder
C5: 10uF; CP_Elec_4x3.9
H1, H2, H3, H4: MountingHole_Pad; MountingHole_2.5mm_Pad_TopBottom
I_Audio_Out_Tx: Conn_01x02_Socket; JST_EH_B2B-EH-A_1x02_P2.50mm_Vertical
I_Rx: Conn_01x02_Socket; JST_EH_B2B-EH-A_1x02_P2.50mm_Vertical
Q_Audio_Out_Tx: Conn_01x02_Socket; JST_EH_B2B-EH-A_1x02_P2.50mm_Vertical
Q_Rx: Conn_01x02_Socket; JST_EH_B2B-EH-A_1x02_P2.50mm_Vertical
R1, R2: R; R_0805_2012Metric_Pad1.20x1.40mm_HandSolder
R3, R4, R5, R6, R7, R8, R9, R10, R11, R12, R13, R14, R15, R16, R17, R18, R19, R20, R21, R22, R23, R24, R25, R26, R27, R28, R29, R30: 10k; R_0805_2012Metric_Pad1.20x1.40mm_HandSolder
S1, S2, S3, S5, S6, S7, S8, S9, S10, S11, S12: SM-3TW103; SM3TW103
S4: 8x SM-3TW103; SM3TW103
Supply: Conn_01x02_Socket; JST_EH_B2B-EH-A_1x02_P2.50mm_Vertical
Tx: Conn_01x02_Socket; JST_EH_B2B-EH-A_1x02_P2.50mm_Vertical
U1: 5x OPA1678IDGKT; OPA1678_L
U2: LM358_DFN; DFN-8-1EP_2x2mm_P0.5mm_EP1.05x1.75mm
U3: 2x 74HC4052_SNM; TSSOP16_5P1X4P5_NEX
U4, U5, U6, U7: OPA1678IDGKT; OPA1678_L
U8: 74HC4052_SNM; TSSOP16_5P1X4P5_NEX
USB_LSB: Conn_01x02_Socket; JST_EH_B2B-EH-A_1x02_P2.50mm_Vertical

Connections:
+5V: C1.1, C3.2, R1.1, Supply.2, U1.8 (V+), U2.8 (V+), U3.16 (VDD), U4.8 (V+), U5.8 (V+), U6.8 (V+), U7.8 (V+), U8.16 (VDD)
/Tx: R30.2, Tx.2, U3.9 (B), U8.9 (B)
/USB_LSB: R23.2, U3.10 (A), U8.10 (A), USB_LSB.2
/Vref: C4.2, C5.1, R3.2, R4.2, S3.2 (WIPER), S3.3 (CW), S4.2 (WIPER), S4.3 (CW), S5.2 (WIPER), S5.3 (CW), S6.2 (WIPER), S6.3 (CW), S7.2 (WIPER), S7.3 (CW), S8.2 (WIPER), S8.3 (CW), S9.2 (WIPER), S9.3 (CW), S10.2 (WIPER), S10.3 (CW), U2.1, U2.2 (-)
GND: Audio_In_Tx.1, Audio_Out_Rx.1, C1.2, C3.1, H1.1, H2.1, H3.1, H4.1, I_Audio_Out_Tx.1, I_Rx.1, Q_Audio_Out_Tx.1, Q_Rx.1, R23.1, R30.1, Supply.1, Tx.1, U1.4 (V-), U2.4 (V-), U2.9 (PAD), U3.6 (INH), U3.7 (VEE), U3.8 (VSS), U4.4 (V-), U5.4 (V-), U6.4 (V-), U7.4 (V-), U8.6 (INH), U8.7 (VEE), U8.8 (VSS), USB_LSB.1
unnamed: Audio_In_Tx.2, S1.2 (WIPER), S2.2 (WIPER)
unnamed: Audio_Out_Rx.2, S11.2 (WIPER), S12.2 (WIPER)
unnamed: C2.1, C4.1, C5.2, R2.2
unnamed: I_Audio_Out_Tx.2, U8.5 (Y1), U8.12 (X0)
unnamed: I_Rx.2, U3.4 (Y3), U3.15 (X2)
unnamed: Q_Audio_Out_Tx.2, U8.1 (Y0), U8.14 (X1)
unnamed: Q_Rx.2, U3.2 (Y2), U3.11 (X3)
unnamed: S1.1 (CCW), U3.5 (Y1)
unnamed: S1.3 (CW), U3.14 (X1)
unnamed: S2.1 (CCW), U3.1 (Y0)
unnamed: S2.3 (CW), U3.12 (X0)
unnamed: R7.2, S3.1 (CCW)
unnamed: R8.2, S4.1 (CCW)
unnamed: R13.2, S5.1 (CCW)
unnamed: R14.2, S6.1 (CCW)
unnamed: R19.2, S7.1 (CCW)
unnamed: R20.2, S8.1 (CCW)
unnamed: R26.2, S9.1 (CCW)
unnamed: R27.2, S10.1 (CCW)
unnamed: S11.1 (CCW), U8.15 (X2)
unnamed: S11.3 (CW), U8.2 (Y2)
unnamed: S12.1 (CCW), U8.11 (X3)
unnamed: S12.3 (CW), U8.4 (Y3)
unnamed: R3.1, U1.3 (IN+), U3.13 (X)
unnamed: C6.1, R5.1, U1.1 (OUT), U1.2 (IN-)
unnamed: R4.1, U1.5 (IN+), U3.3 (Y)
unnamed: C7.1, R6.1, U1.6 (IN-), U1.7 (OUT)
unnamed: C2.2, R1.2, R2.1, U2.3 (+)
unnamed: C6.2, R7.1, U4.3 (IN+)
unnamed: R5.2, R9.1, U4.2 (IN-)
unnamed: C8.1, R9.2, R11.1, U4.1 (OUT)
unnamed: C8.2, R13.1, U4.5 (IN+)
unnamed: R11.2, R15.1, U4.6 (IN-)
unnamed: C10.1, R15.2, R17.1, U4.7 (OUT)
unnamed: C7.2, R8.1, U5.3 (IN+)
unnamed: R6.2, R10.1, U5.2 (IN-)
unnamed: C9.1, R10.2, R12.1, U5.1 (OUT)
unnamed: C9.2, R14.1, U5.5 (IN+)
unnamed: R12.2, R16.1, U5.6 (IN-)
unnamed: C11.1, R16.2, R18.1, U5.7 (OUT)
unnamed: C10.2, R19.1, U6.3 (IN+)
unnamed: R17.2, R21.1, U6.2 (IN-)
unnamed: C12.1, R21.2, R24.1, U6.1 (OUT)
unnamed: C12.2, R26.1, U6.5 (IN+)
unnamed: R24.2, R28.1, U6.6 (IN-)
unnamed: R28.2, U6.7 (OUT), U8.13 (X)
unnamed: C11.2, R20.1, U7.3 (IN+)
unnamed: R18.2, R22.1, U7.2 (IN-)
unnamed: C13.1, R22.2, R25.1, U7.1 (OUT)
unnamed: C13.2, R27.1, U7.5 (IN+)
unnamed: R25.2, R29.1, U7.6 (IN-)
unnamed: R29.2, U7.7 (OUT), U8.3 (Y)

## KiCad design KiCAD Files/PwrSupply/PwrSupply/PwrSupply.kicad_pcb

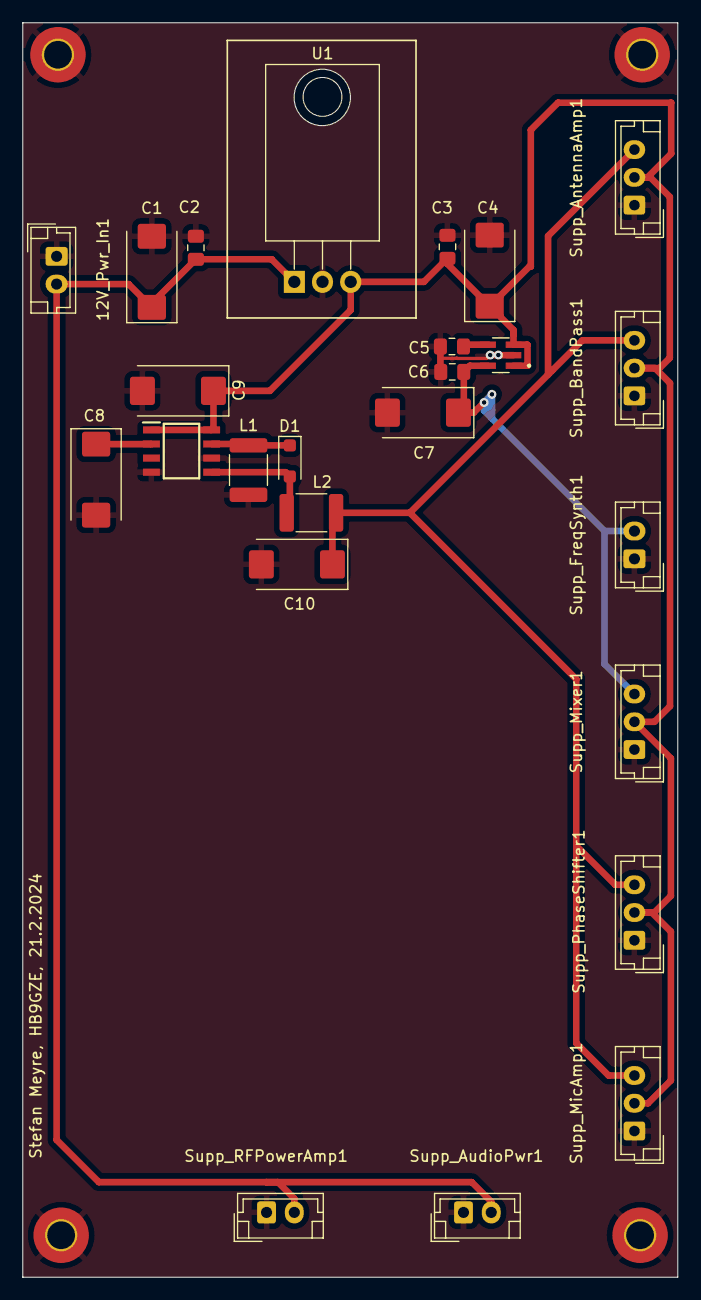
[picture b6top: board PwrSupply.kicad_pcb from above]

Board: 2 copper layers, 59.0 x 113.0 mm, 28 parts (0 on the bottom side), 8 nets.

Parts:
12V_Pwr_In1: 12V_Pwr_In; JST_EH_B2B-EH-A_1x02_P2.50mm_Vertical
C1, C4: 47uF Tant. 25V; CP_EIA-7343-30_AVX-N_Pad2.25x2.55mm_HandSolder
C2, C3, C6: 100nF; C_0805_2012Metric_Pad1.18x1.45mm_HandSolder
C5: 1uF; C_0805_2012Metric_Pad1.18x1.45mm_HandSolder
C7, C8: 10uF Tant. 25V; CP_EIA-7343-30_AVX-N_Pad2.25x2.55mm_HandSolder
C9: 1uF, Tant. 25V; CP_EIA-7343-30_AVX-N_Pad2.25x2.55mm_HandSolder
C10: 100uF Tant. 25V; CP_EIA-7343-30_AVX-N_Pad2.25x2.55mm_HandSolder
D1: PMEG2010AEH; D_SOD-123F
H1, H2, H3, H4: MountingHole_Pad; MountingHole_2.5mm_Pad_TopBottom
IC1: NCP700BSN33T1G; SOT95P275X120-5N
L1, L2: 10uH; L_1812_4532Metric_Pad1.30x3.40mm_HandSolder
Supp_AntennaAmp1: Supp_AntennaAmp; JST_EH_B3B-EH-A_1x03_P2.50mm_Vertical
Supp_AudioPwr1: Supp_FreqSynth; JST_EH_B2B-EH-A_1x02_P2.50mm_Vertical
Supp_BandPass1: Supp_BandPass; JST_EH_B3B-EH-A_1x03_P2.50mm_Vertical
Supp_FreqSynth1: Supp_FreqSynth; JST_EH_B2B-EH-A_1x02_P2.50mm_Vertical
Supp_MicAmp1: Supp_MicAmp; JST_EH_B3B-EH-A_1x03_P2.50mm_Vertical
Supp_Mixer1: Supp_Mixer; JST_EH_B3B-EH-A_1x03_P2.50mm_Vertical
Supp_PhaseShifter1: Supp_PhaseShifter; JST_EH_B3B-EH-A_1x03_P2.50mm_Vertical
Supp_RFPowerAmp1: Supp_FreqSynth; JST_EH_B2B-EH-A_1x02_P2.50mm_Vertical
U1: L7805; TO-220-3_Horizontal_TabDown

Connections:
+3.3V: C6.1, C7.1, IC1.5 (OUT), Supp_FreqSynth1.2, Supp_Mixer1.3
+5V: C3.1, C4.1, C9.1, IC1.1 (IN), IC1.3 (EN), Supp_AntennaAmp1.2, Supp_BandPass1.2, Supp_MicAmp1.2, Supp_Mixer1.2, Supp_PhaseShifter1.2, U1.3 (OUT)
+12V: 12V_Pwr_In1.2, C1.1, C2.1, Supp_AudioPwr1.2, Supp_RFPowerAmp1.2, U1.1 (IN)
-5V: C10.1, L2.2, Supp_AntennaAmp1.3, Supp_BandPass1.3, Supp_MicAmp1.3, Supp_PhaseShifter1.3
GND: 12V_Pwr_In1.1, C1.2, C2.2, C3.2, C4.2, C5.1, C6.2, C7.2, C8.2, C9.2, C10.2, H1.1, H2.1, H3.1, H4.1, IC1.2 (GND), L1.2, Supp_AntennaAmp1.1, Supp_AudioPwr1.1, Supp_BandPass1.1, Supp_FreqSynth1.1, Supp_MicAmp1.1, Supp_Mixer1.1, Supp_PhaseShifter1.1, Supp_RFPowerAmp1.1, U1.2 (GND)
unnamed: D1.2 (A), L2.1
unnamed: D1.1 (K), L1.1
unnamed: C5.2, IC1.4 (BYP)
